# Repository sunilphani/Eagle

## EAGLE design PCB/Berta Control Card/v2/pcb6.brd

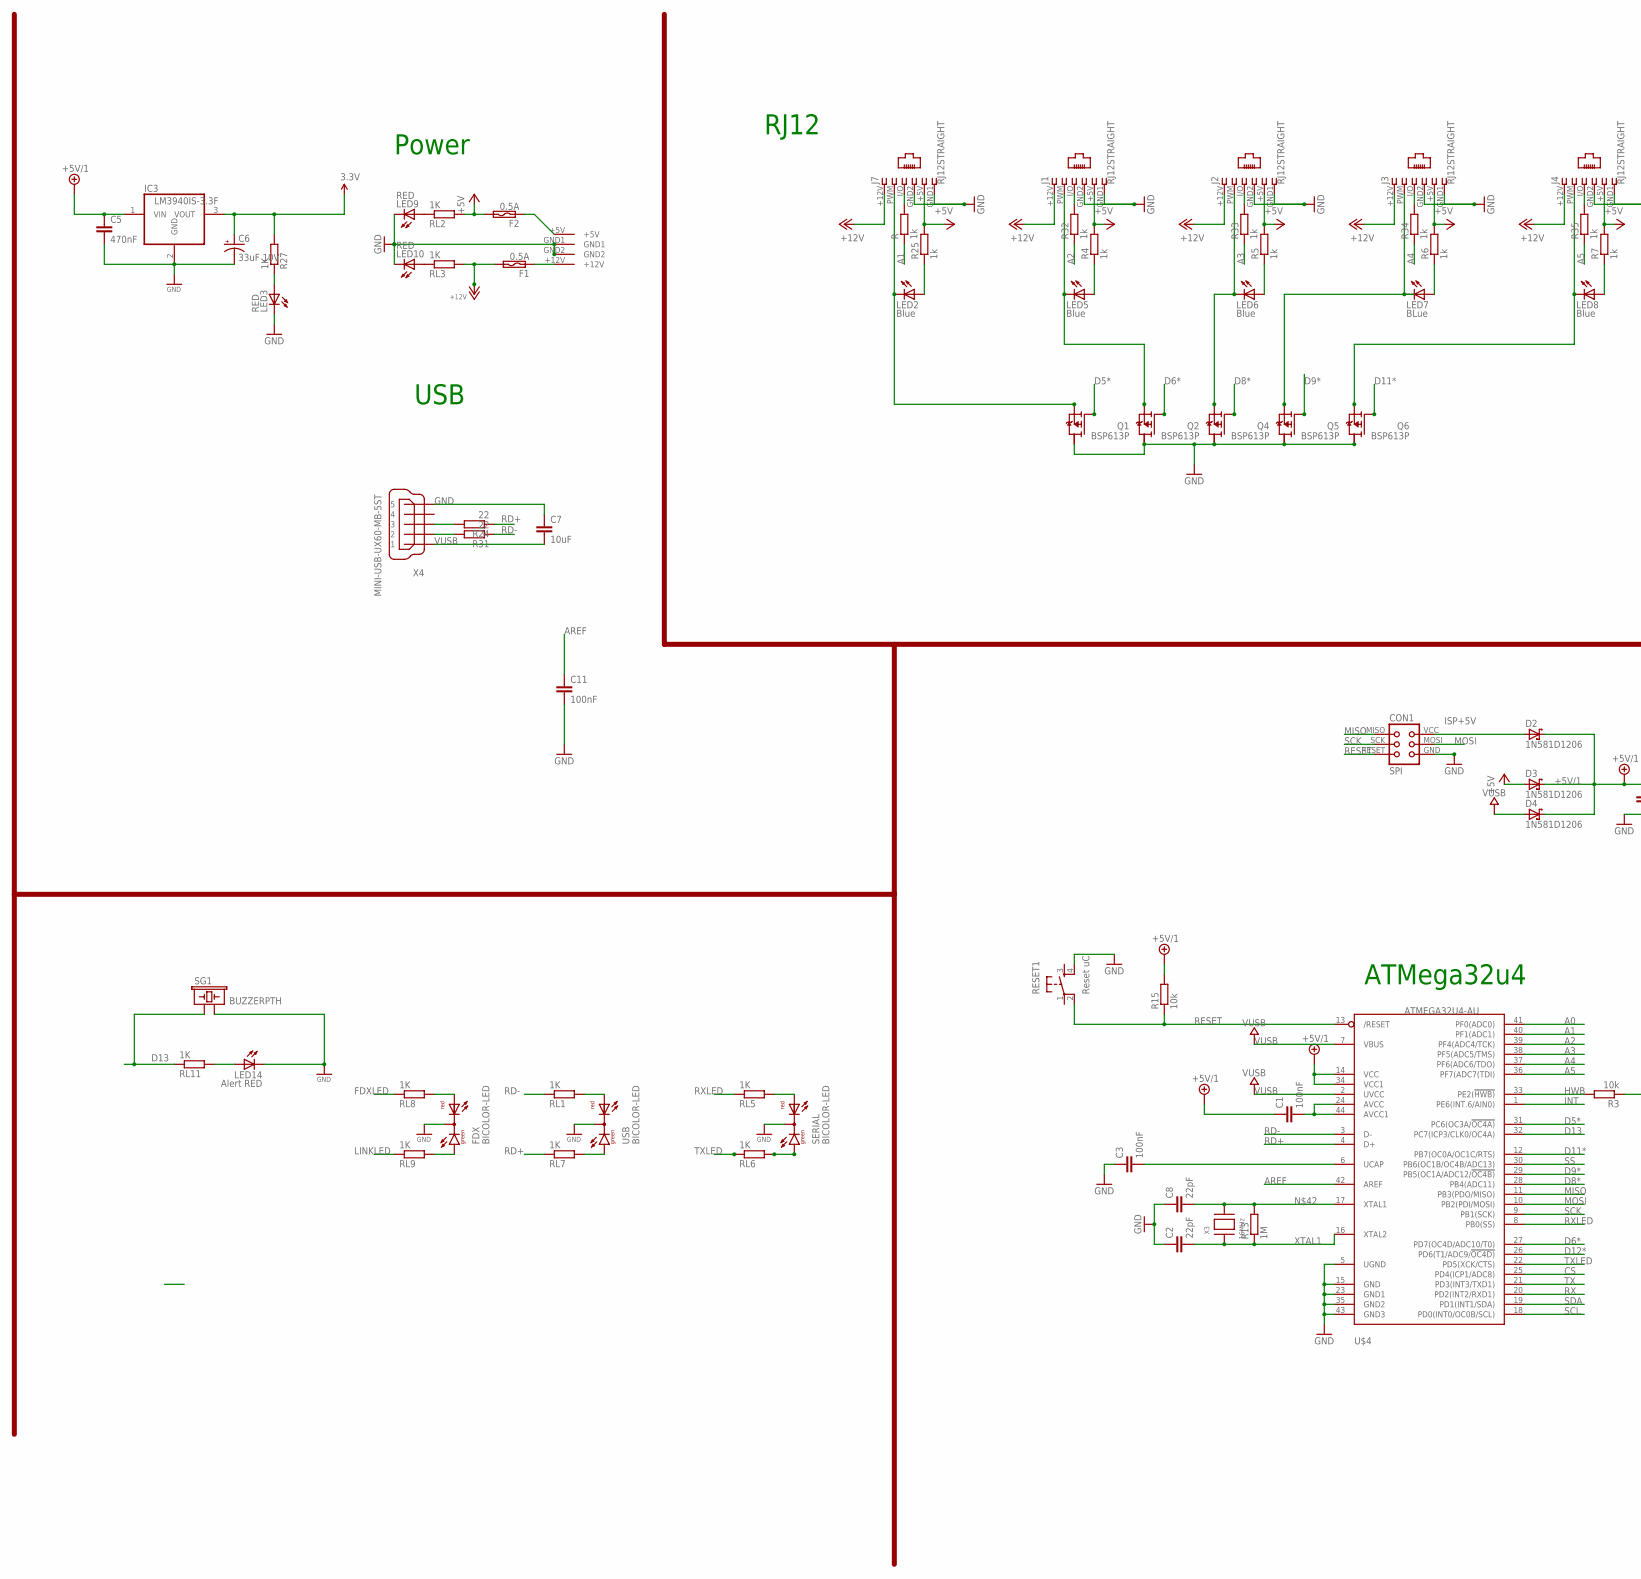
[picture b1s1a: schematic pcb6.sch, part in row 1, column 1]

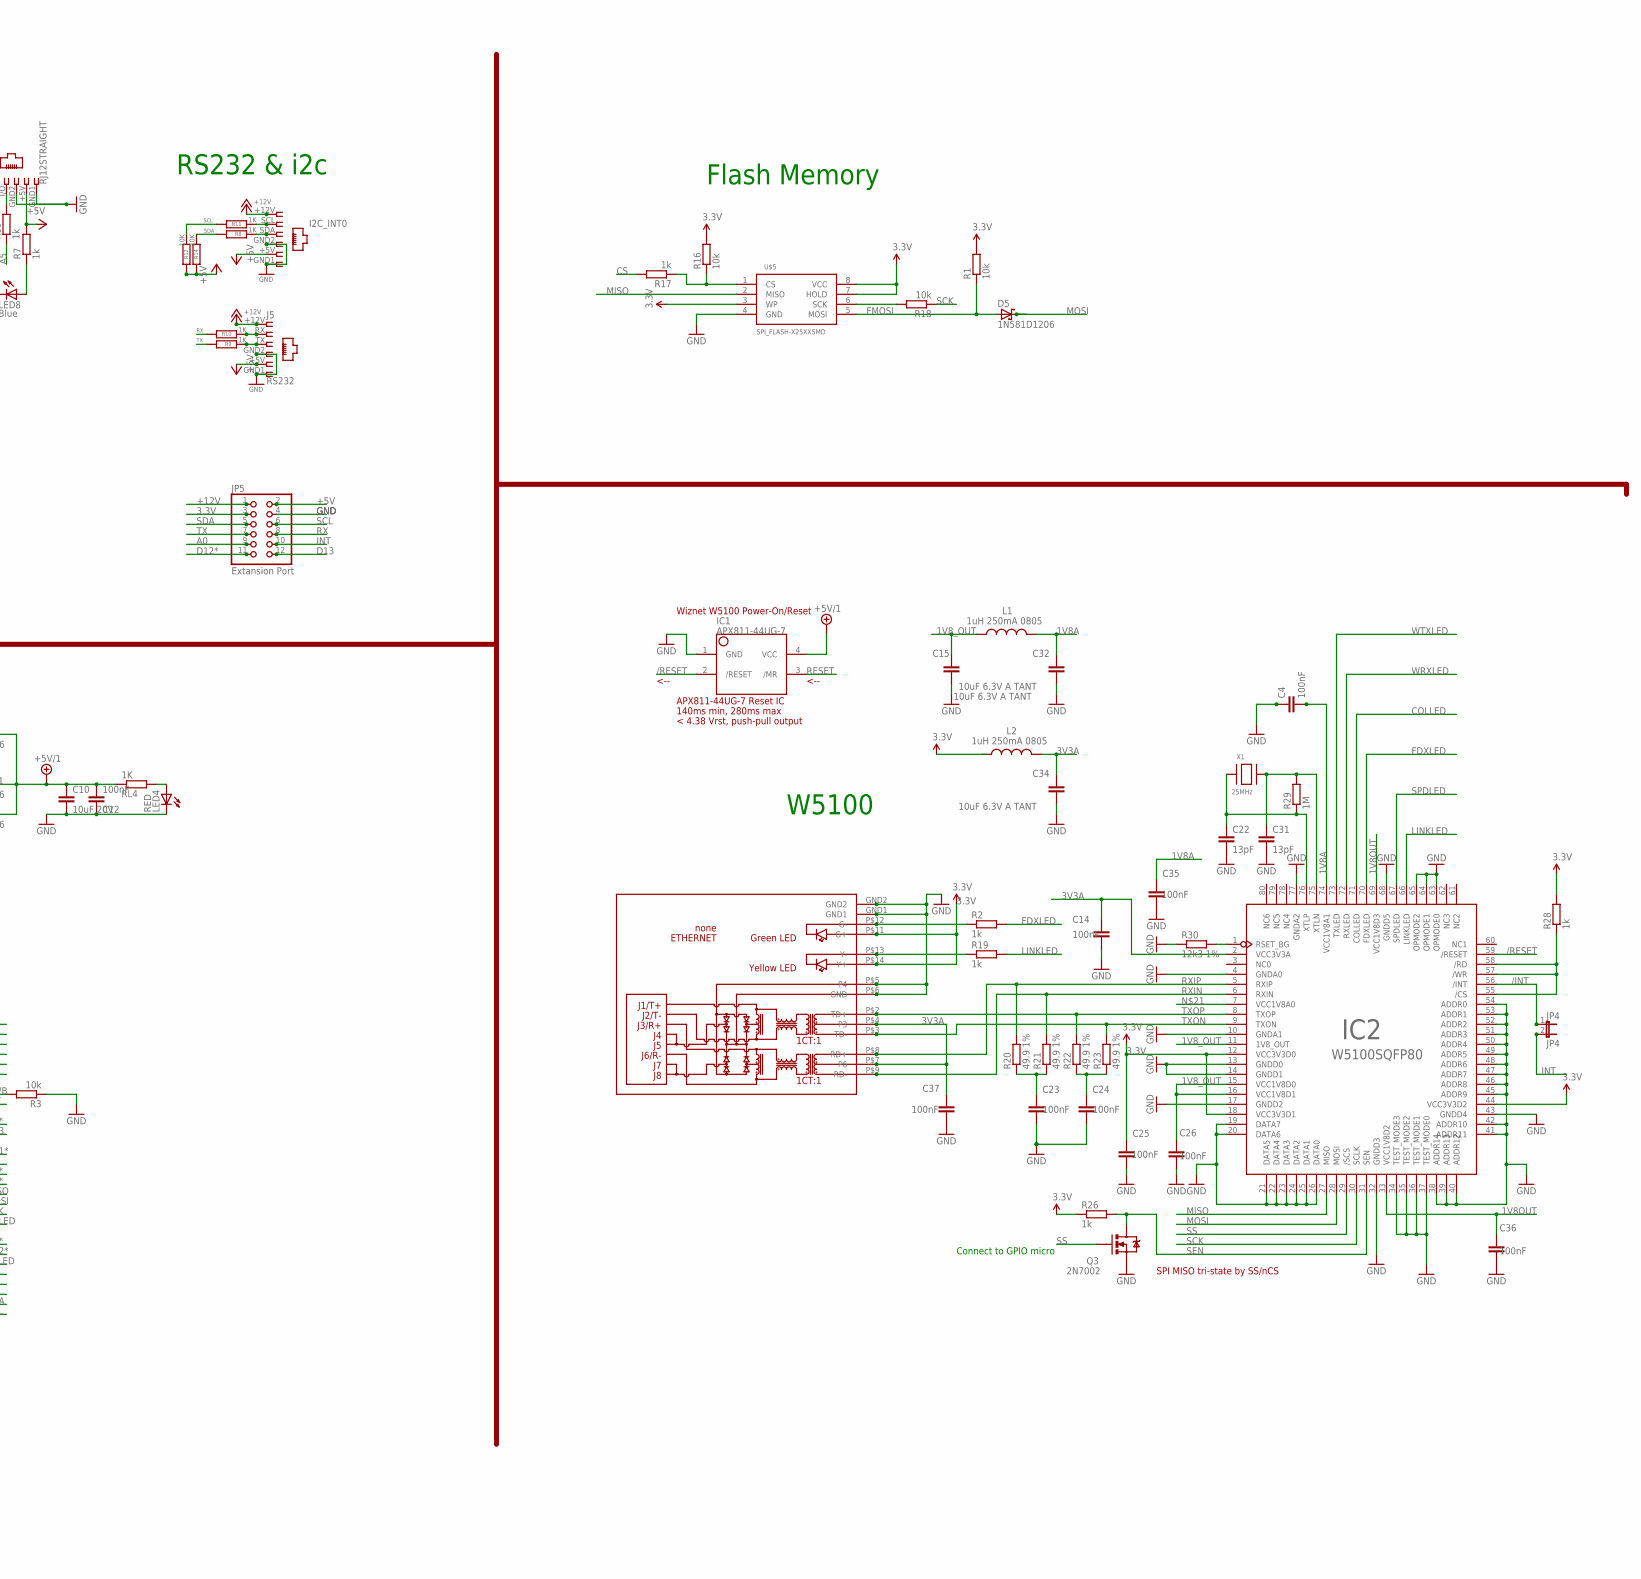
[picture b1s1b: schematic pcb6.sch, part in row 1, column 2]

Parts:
C1, C3, C4, C11, C12, C14, C23, C24, C25, C26, C35, C36, C37: 100nF; C1206
C2, C8: 22pF; C1206
C5: 470nF; C1206
C6: 33uF 10V; EIA7343
C7: 10uF; C1206
C10: 10uF 20V; C1206
C15, C32, C34: 10uF 6.3V A TANT; C1206
C22, C31: 13pF; C1206
CON1: SPI; TINYISP
D2, D3, D4, D5: 1N581D1206; LED-1206
ETHERNET: none; HY931147C
F1, F2: 0.5A; C1812
FDX: BICOLOR-LED; BICOLOR-3MM
I2C_INT0: I2C; RJ12-STRAIGHT-I2C
IC1: APX811-44UG-7; SOT143-R
IC2: W5100SQFP80; SQFP80
IC3: LM3940IS-3.3F; DD-3
J1, J2, J3, J4, J7: RJ12STRAIGHT; RJ12-STRAIGHT
J5: RS232; RJ12-STRAIGHT-RS232
JP4: JP4; 1X02
JP5: Extansion Port; 2X06
L1, L2: 1uH 250mA 0805; L2012C
LED2, LED5, LED6, LED8: Blue; LED3MM
LED3, LED4, LED9, LED10: RED; LED3MM
LED7: BLue; LED3MM
LED14: Alert RED; LED3MM
Q1, Q2, Q4, Q5, Q6: BSP613P; PG-SOT-223
Q3: 2N7002; SOT23-3
R, R2, R4, R5, R6, R7, R17, R19, R25, R26, R28, R32, R33, R34, R35: 1k; R0805
R1, R3, R15, R16, R18: 10k; R1206
R8, R9, R10, R11, R27: 1K; R0805
R12, R14: 10K; R1206
R13, R29: 1M; R1206
R20, R21, R22, R23: 49.9 1%; R0805W
R24, R31: 22; M1206
R30: 12k3 1%; R0805W
RESET1: Reset uC; TACTILE_SWITCH_SMD
RL1, RL2, RL3, RL5, RL6, RL7, RL8, RL9, RL11: 1K; R0805
RL4: 1K; R0805@1
SERIAL: BICOLOR-LED; BICOLOR-3MM
SG1: BUZZERPTH; BUZZER-12MM
U$4: ATMEGA32U4-AU; TQFP44
U$5: SPI_FLASH-X25XXSMD; SO08
U$6: KPJX-4S-S
USB: BICOLOR-LED; BICOLOR-3MM
X1: 25MHz; NX6035
X3: 16MHz; NX6035
X4: MINI-USB-UX60-MB-5ST; UX60-MB-5ST

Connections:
1V8A: C4.2, C32.1, C35.1, IC2.74 (VCC1V8A1), L1.2
1V8OUT: C36.1, IC2.33 (VCC1V8D2), IC2.69 (VCC1V8D3)
1V8_OUT: C15.1, C26.1, IC2.11 (1V8_OUT), IC2.15 (VCC1V8D0), IC2.16 (VCC1V8D1), L1.1
3.3V: C6.A (+), C25.1, ETHERNET.P$11 (G+), ETHERNET.P$14 (Y+), IC2.12 (VCC3V3D0), IC2.18 (VCC3V3D1), IC2.44 (VCC3V3D2), IC3.3 (VOUT), JP5.3, R1.2, R16.2, R26.1, R27.2, R28.2, U$5.3 (WP), U$5.7 (HOLD), U$5.8 (VCC)
3V3A: C14.1, C34.1, C37.1, ETHERNET.P$4 (P3), ETHERNET.P$7 (P6), IC2.2 (VCC3V3A), L2.2
+5V: D3.A, F2.2, I2C_INT0.+5V (5), J1.+5V (5), J2.+5V (5), J3.+5V (5), J4.+5V (5), J5.+5V (5), J7.+5V (5), JP5.2, R4.2, R5.2, R6.2, R7.2, R12.2, R14.2, R25.2, RL2.2
+5V/1: C1.1, C5.1, C10.1, C12.2, D2.C, D3.C, D4.C, IC1.4 (VCC), IC3.1 (VIN), R15.2, RL4.1, U$4.14 (VCC), U$4.34 (VCC1)
+12V: F1.2, I2C_INT0.+12V (1), J1.+12V (1), J2.+12V (1), J3.+12V (1), J4.+12V (1), J5.+12V (1), J7.+12V (1), JP5.1, RL3.2
/INT: IC2.56 (/INT), JP4.1
/RESET: IC1.2 (/RESET), IC2.59 (/RESET)
A0: JP5.9, U$4.41 (PF0(ADC0))
A1: R.1, U$4.40 (PF1(ADC1))
A2: R32.1, U$4.39 (PF4(ADC4/TCK))
A3: R33.1, U$4.38 (PF5(ADC5/TMS))
A4: R34.1, U$4.37 (PF6(ADC6/TDO))
A5: R35.1, U$4.36 (PF7(ADC7(TDI))
AREF: C11.1, U$4.42 (AREF)
COLLED: IC2.71 (COLLED)
CS: R17.2, U$4.25 (PD4(ICP1/ADC8))
D2B4: I2C_INT0.SDA (3), R8.1
D2B5: J5.TX (3), R9.1
D5*: Q1.1 (G), U$4.31 (PC6(OC3A/!OC4A))
D6*: Q2.1 (G), U$4.27 (PD7(OC4D/ADC10/T0))
D8*: Q4.1 (G), U$4.28 (PB4(ADC11))
D9*: Q5.1 (G), U$4.29 (PB5(OC1A/ADC12/!OC4B))
D11*: Q6.1 (G), U$4.12 (PB7(OC0A/OC1C/RTS))
D12*: JP5.11, U$4.26 (PD6(T1/ADC9/!OC4D))
D13: JP5.12, RL11.1, SG1.+ (1), U$4.32 (PC7(ICP3/CLK0/OC4A))
D+USB: R24.2, X4.3
D-USB: R31.2, X4.2
FDXLED: IC2.70 (FDXLED), R2.2, RL8.1
FMOSI: D5.A, R1.1, U$5.5 (MOSI)
GND: C2.1, C3.1, C4.1, C5.2, C6.C (-), C7.1, C8.1, C10.2, C11.2, C12.1, C14.2, C15.2, C22.2, C23.2, C24.2, C25.2, C26.2, C31.2, C32.2, C34.2, C35.2, C36.2, C37.2, CON1.GND, ETHERNET.GND1, ETHERNET.GND2, ETHERNET.P$5 (P4), ETHERNET.P$6 (GND), FDX.2 (C), I2C_INT0.GND1 (6), I2C_INT0.GND2 (4), IC1.1 (GND), IC2.4 (GNDA0), IC2.10 (GNDA1), IC2.13 (GNDD0), IC2.14 (GNDD1), IC2.17 (GNDD2), IC2.19 (DATA7), IC2.20 (DATA6), IC2.21 (DATA5), IC2.22 (DATA4), IC2.23 (DATA3), IC2.24 (DATA2), IC2.25 (DATA1), IC2.26 (DATA0), IC2.32 (GNDD3), IC2.34 (TEST_MODE3), IC2.35 (TEST_MODE2), IC2.36 (TEST_MODE1), IC2.37 (TEST_MODE0), IC2.38 (ADDR14), IC2.39 (ADDR13), IC2.40 (ADDR12), IC2.41 (ADDR11), IC2.42 (ADDR10), IC2.43 (GNDD4), IC2.45 (ADDR9), IC2.46 (ADDR8), IC2.47 (ADDR7), IC2.48 (ADDR6), IC2.49 (ADDR5), IC2.50 (ADDR4), IC2.51 (ADDR3), IC2.52 (ADDR2), IC2.53 (ADDR1), IC2.54 (ADDR0), IC2.63 (OPMODE0), IC2.64 (OPMODE1), IC2.65 (OPMODE2), IC2.68 (GNDD5), IC2.77 (GNDA2), IC3.2 (GND), J1.GND1 (6), J1.GND2 (4), J2.GND1 (6), J2.GND2 (4), J3.GND1 (6), J3.GND2 (4), J4.GND1 (6), J4.GND2 (4), J5.GND1 (6), J5.GND2 (4), J7.GND1 (6), J7.GND2 (4), JP5.4, LED3.K (C), LED4.K (C), LED9.K (C), LED10.K (C), LED14.K (C), Q1.2 (D), Q2.2 (D), Q3.2 (S), Q4.2 (D), Q5.2 (D), Q6.2 (D), R3.1, R30.1, RESET1.4, SERIAL.2 (C), SG1.- (2), U$4.5 (UGND), U$4.15 (GND), U$4.23 (GND1), U$4.35 (GND2), U$4.43 (GND3), U$5.4 (GND), U$6.GND1, U$6.GND2, USB.2 (C), X4.5
HWB: R3.2, U$4.33 (PE2(!HWB))
INT: JP4.2, JP5.10, U$4.1 (PE6(INT.6/AIN0))
ISP+5V: CON1.VCC, D2.A
LINKLED: IC2.66 (LINKLED), R19.2, RL9.1
MISO: CON1.MISO, IC2.27 (MISO), U$4.11 (PB3(PDO/MISO)), U$5.2 (MISO)
MOSI: CON1.MOSI, D5.C, IC2.28 (MOSI), U$4.10 (PB2(PDI/MOSI))
unnamed: J2.PWM (2), LED6.K (C), Q4.3 (S)
unnamed: J1.I/O (3), R32.2
unnamed: C1.2, U$4.24 (AVCC), U$4.44 (AVCC1)
unnamed: LED5.A, R4.1
unnamed: J3.PWM (2), LED7.K (C), Q5.3 (S)
unnamed: FDX.3 (AR), RL8.2
unnamed: J2.I/O (3), R33.2
unnamed: RL1.2, USB.3 (AR)
unnamed: C24.1, R22.1, R23.1
unnamed: R16.1, R17.1, U$5.1 (CS)
unnamed: FDX.1 (AG), RL9.2
unnamed: LED4.A, RL4.2
unnamed: RL5.2, SERIAL.3 (AR)
unnamed: RL7.2, USB.1 (AG)
unnamed: RL6.2, SERIAL.1 (AG)
unnamed: C3.2, U$4.6 (UCAP)
unnamed: LED2.A, R25.1
unnamed: J7.I/O (3), R.2
unnamed: J4.PWM (2), LED8.K (C), Q6.3 (S)
unnamed: LED3.A, R27.1
unnamed: LED6.A, R5.1
unnamed: R18.2, U$5.6 (SCK)
unnamed: IC2.55 (/CS), IC2.57 (/WR), IC2.58 (/RD), R28.1
unnamed: LED14.A, RL11.2
unnamed: J1.PWM (2), LED5.K (C), Q2.3 (S)
unnamed: J3.I/O (3), R34.2
unnamed: LED7.A, R6.1
unnamed: J4.I/O (3), R35.2
unnamed: LED8.A, R7.1
unnamed: J7.PWM (2), LED2.K (C), Q1.3 (S)
unnamed: F2.1, U$6.+5V
unnamed: F1.1, U$6.+12V
unnamed: C8.2, R13.2, U$4.17 (XTAL1), X3.P$2
unnamed: ETHERNET.P$12 (G-), R2.1
unnamed: J5.RX (2), R10.1
unnamed: I2C_INT0.SCL (2), R11.1
unnamed: LED10.A, RL3.1
unnamed: LED9.A, RL2.1
unnamed: C23.1, R20.1, R21.1
unnamed: IC2.1 (RSET_BG), R30.2
unnamed: ETHERNET.P$13 (Y-), R19.1
RD+: R24.1, RL7.1, U$4.4 (D+)
RD-: R31.1, RL1.1, U$4.3 (D-)
RESET: CON1.RESET, IC1.3 (/MR), R15.1, RESET1.2, U$4.13 (/RESET)
RX: JP5.8, R10.2, U$4.20 (PD2(INT2/RXD1))
RXIN: ETHERNET.P$9 (RD-), IC2.6 (RXIN), R21.2
RXIP: ETHERNET.P$8 (RD+), IC2.5 (RXIP), R20.2
RXLED: RL5.1, U$4.8 (PB0(SS))
SCK: CON1.SCK, IC2.30 (SCLK), R18.1, U$4.9 (PB1(SCK))
SCL: JP5.6, R11.2, R12.1, U$4.18 (PD0(INT0/OC0B/SCL))
SDA: JP5.5, R8.2, R14.1, U$4.19 (PD1(INT1/SDA))
SEN: IC2.31 (SEN), Q3.3 (D), R26.2
SPDLED: IC2.67 (SPDLED)
SS: IC2.29 (/SCS), Q3.1 (G), U$4.30 (PB6(OC1B/OC4B/ADC13))
TX: JP5.7, R9.2, U$4.21 (PD3(INT3/TXD1))
TXLED: RL6.1, U$4.22 (PD5(XCK/CTS))
TXON: ETHERNET.P$3 (TD-), IC2.9 (TXON), R23.2
TXOP: ETHERNET.P$2 (TD+), IC2.8 (TXOP), R22.2
VUSB: C7.2, D4.A, U$4.2 (UVCC), U$4.7 (VBUS), X4.1
WRXLED: IC2.72 (RXLED)
WTXLED: IC2.73 (TXLED)
XTAL1: C2.2, R13.1, U$4.16 (XTAL2), X3.P$1
XTLN: C31.1, IC2.75 (XTLN), R29.2, X1.P$2
XTLP: C22.1, IC2.76 (XTLP), R29.1, X1.P$1

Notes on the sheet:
Flash Memory
RJ12
ATMega32u4
W5100
USB
Power
RS232 & i2c
SPI MISO tri-state by SS/nCS
Connect to GPIO micro
APX811-44UG-7 Reset IC
140ms min, 280ms max
Wiznet W5100 Power-On/Reset
< 4.38 Vrst, push-pull output
<--

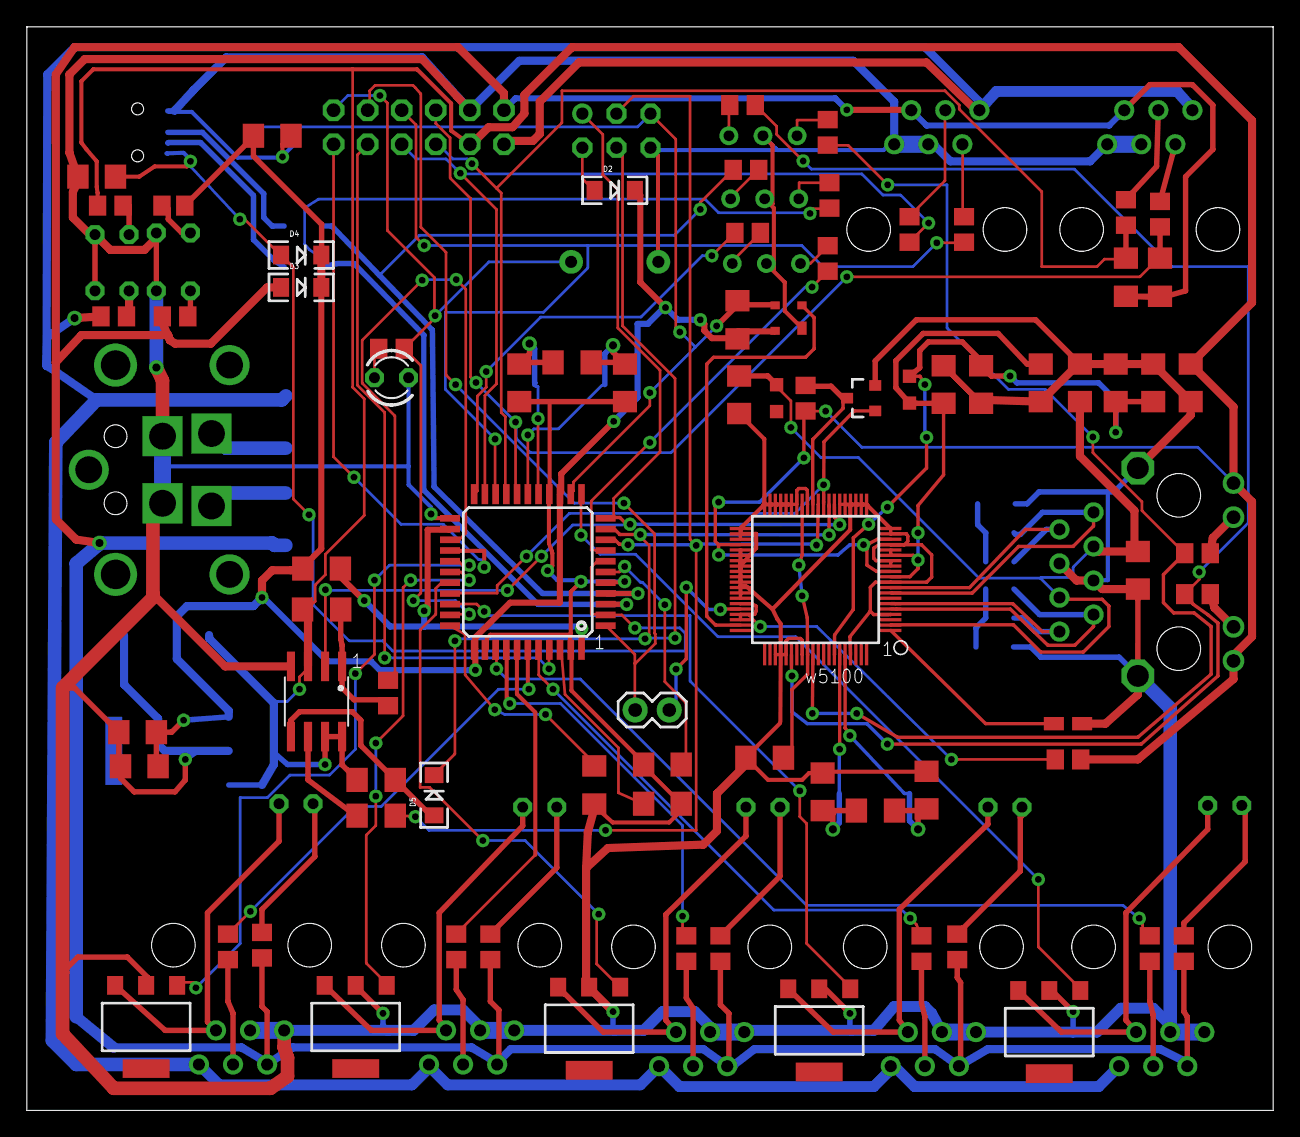
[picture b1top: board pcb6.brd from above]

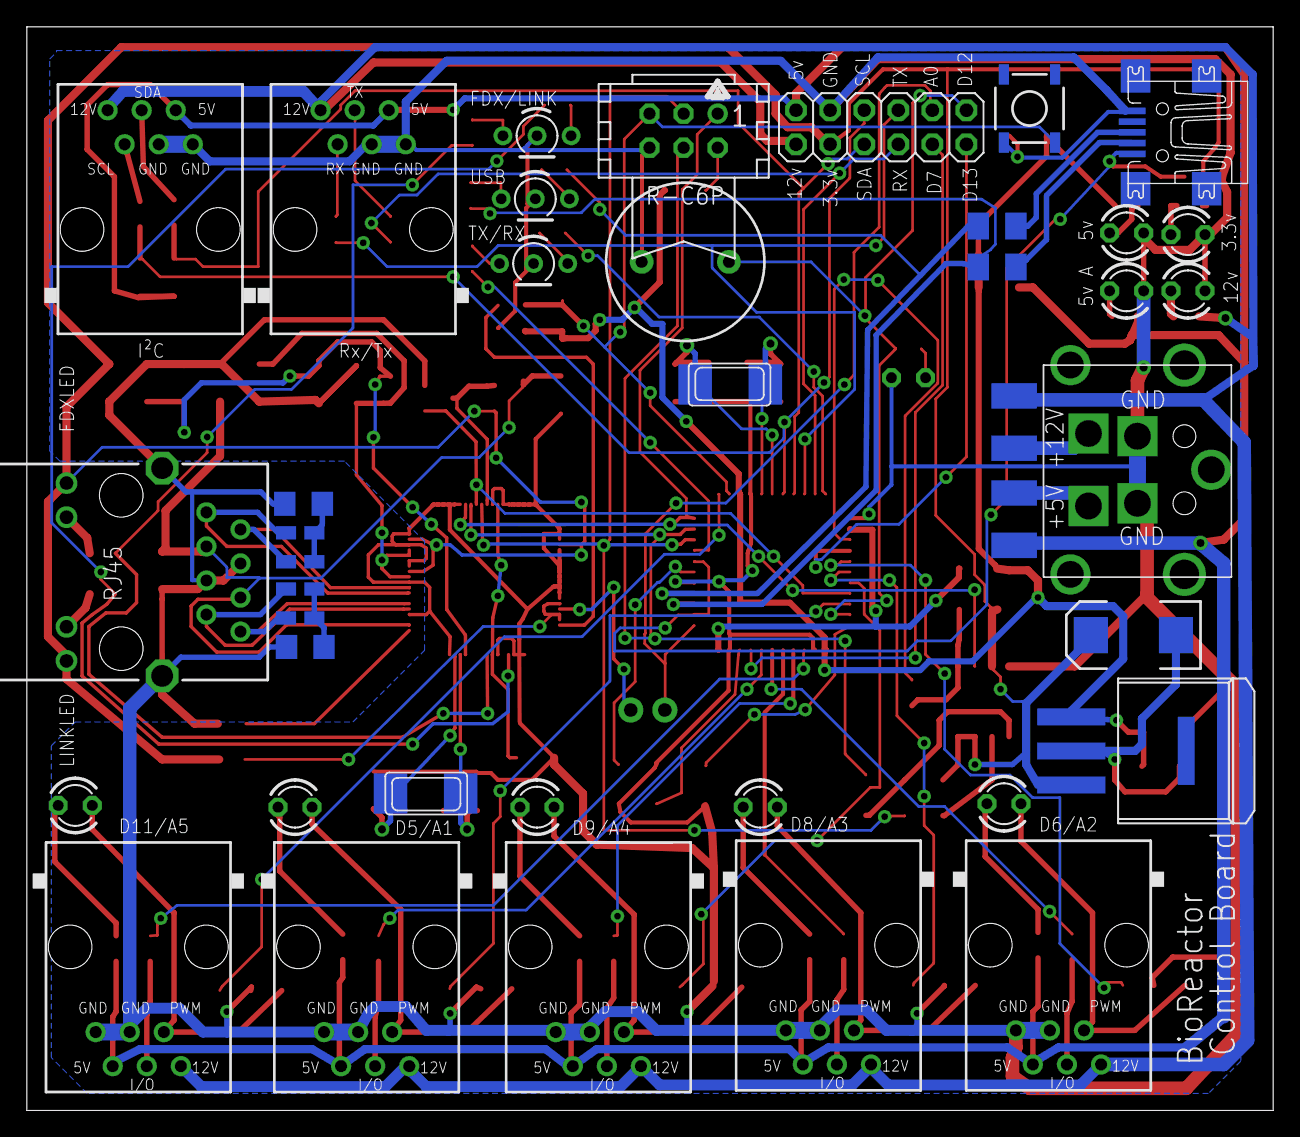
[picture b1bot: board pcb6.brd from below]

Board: 2 copper layers, 92.9 x 80.8 mm, 119 parts (40 on the bottom side), 99 nets.

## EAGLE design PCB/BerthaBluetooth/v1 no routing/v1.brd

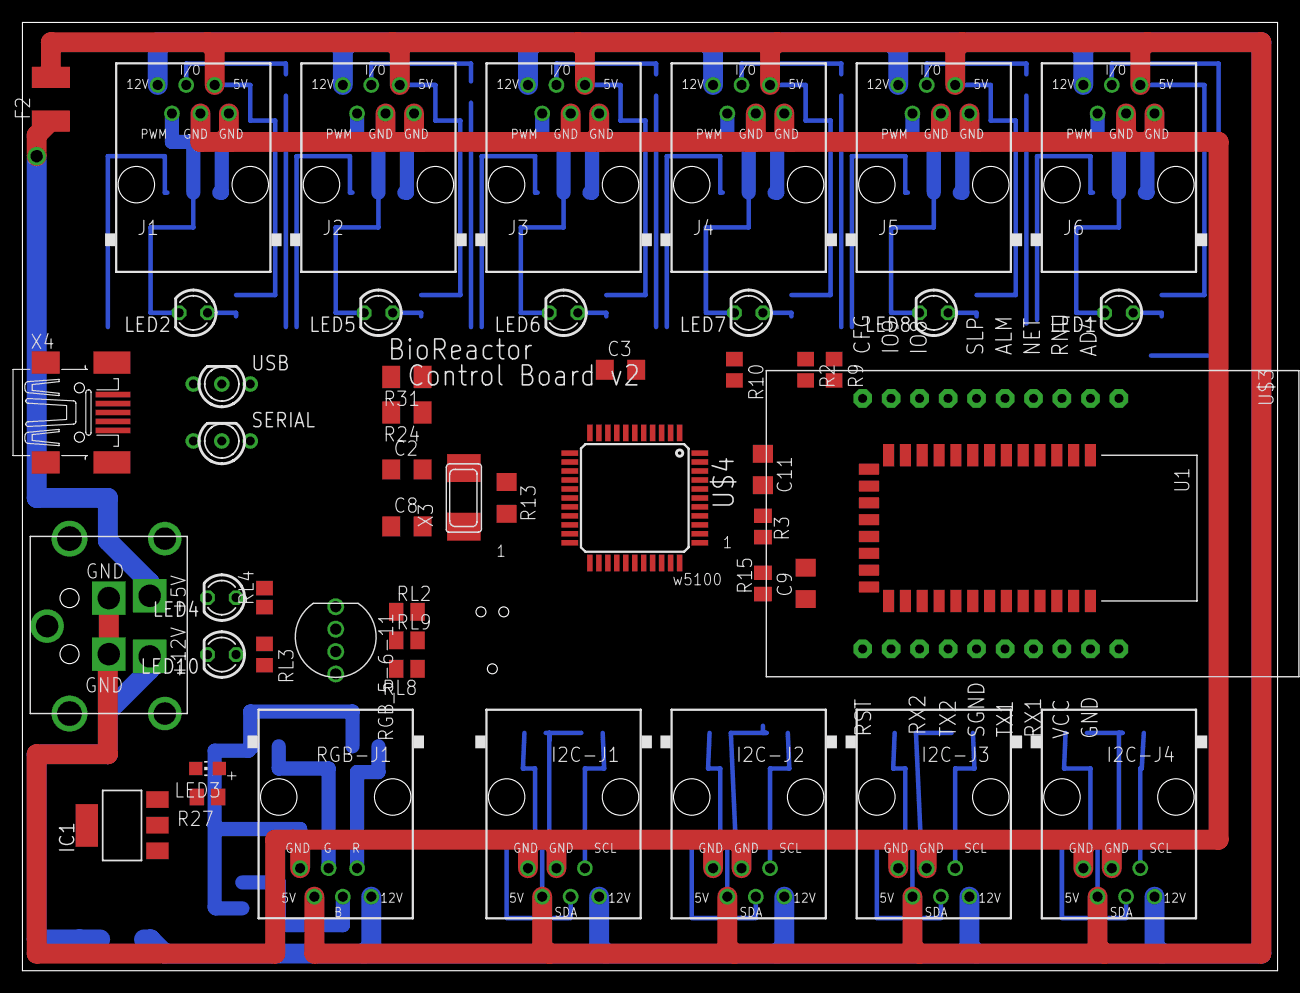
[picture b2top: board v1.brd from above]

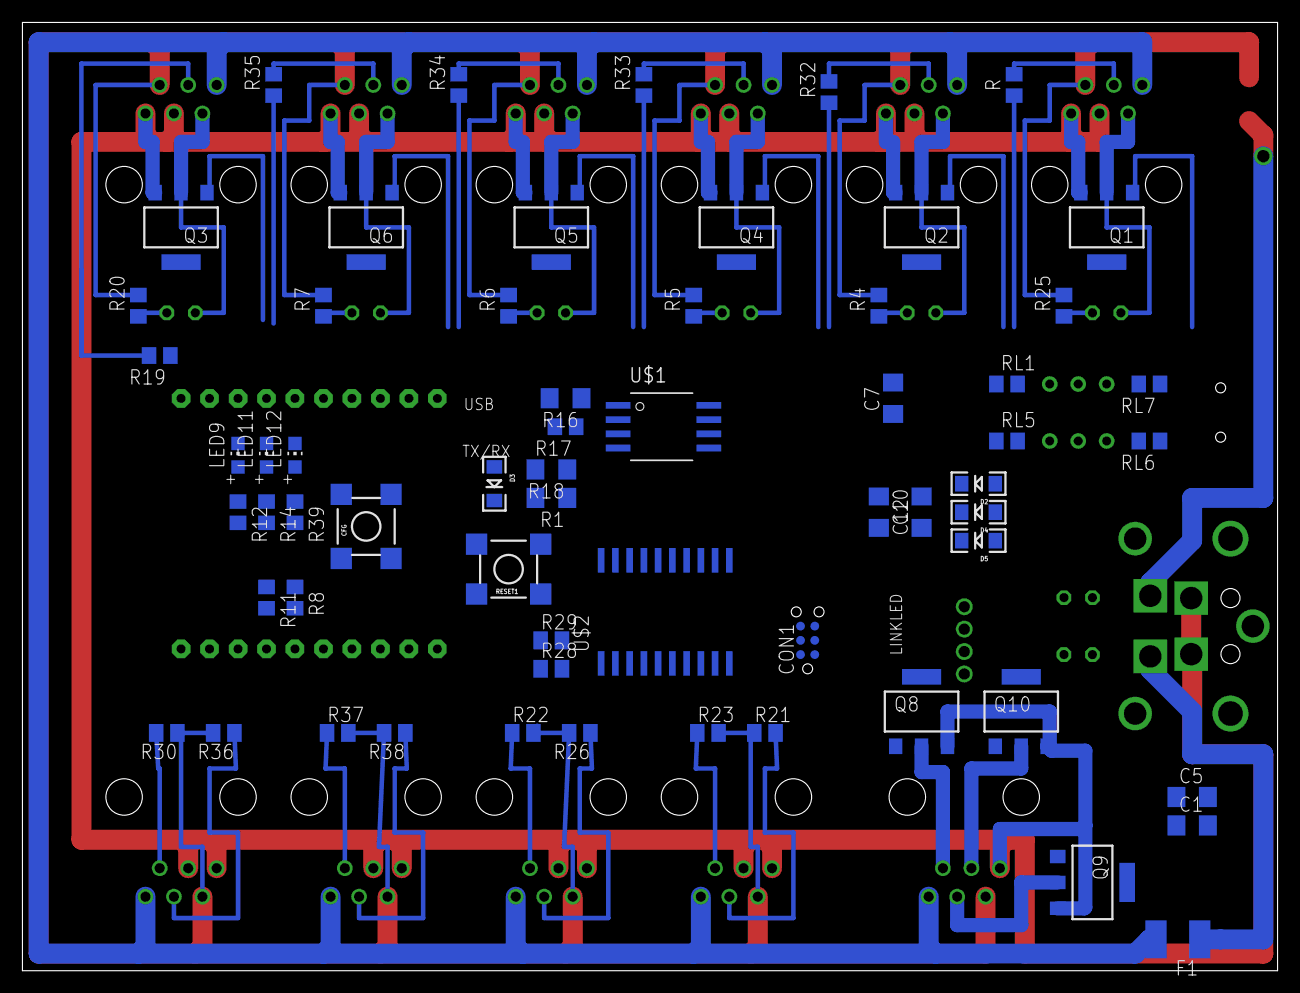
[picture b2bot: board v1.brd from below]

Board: 2 copper layers, 111.9 x 84.6 mm, 112 parts (62 on the bottom side), 97 nets.

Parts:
C1, C5, C7, C10: 10uF; C1206
C2, C8: 22pF; C1206
C3, C9, C11, C12: 100nF; C1206
CFG: Configure; TACTILE_SWITCH_SMD
CON1: SPI; TC2030-MCP-NL
D2, D3, D4, D5: 1N581D1206; LED-1206
F1, F2: 0.5A; C1812
I2C-J1, I2C-J2, I2C-J3, I2C-J4: RJ12STRAIGHT-I2C; RJ12-STRAIGHT-I2C
IC1: REG1117; SOT223
J1, J2, J3, J4, J5, J6: RJ12; RJ12-STRAIGHT
LED1, LED2, LED5, LED6, LED8: Blue; LED3MM
LED3, LED9, LED11, LED12: RED; CHIP-LED0805
LED4, LED10: RED; LED3MM
LED7: BLue; LED3MM
Q1, Q2, Q3, Q4, Q5, Q6, Q8, Q9, Q10: BSP613P; PG-SOT-223
R, R4, R6, R7, R17, R19, R20, R32, R34, R35: 1k; R0805
R1, R16, R18: 10k; R1206
R2: 2.2K; R0805
R3, R15: 10k; M0805
R5, R25, R33: RJ12; R0805
R8, R10, R11, R12, R14, R27, R39: 1K; R0805
R9: 1.2K; R0805
R13: 1M; R1206
R21, R22, R23, R26, R28, R29, R30, R36, R37, R38: 10K; M0805
R24, R31: 22; M1206
RESET1: Reset uC; TACTILE_SWITCH_SMD
RGB-J1: RJ12; RJ12-STRAIGHT-RGB
RGB_5-6-11: LED-TRICOLOR-THROUGHHOLE
RL1, RL3, RL4, RL5, RL6, RL7: 1K; R0805
RL2, RL8, RL9: 1K; M0805
SERIAL: BICOLOR-LED; BICOLOR-3MM
U1: HC_05; BLUETOOTH_SMD
U$1: SST25VF064C; SOIC_8-LEAD
U$2: PCA9518; SO20W
U$3: SZ05-ZIGBEE
U$4: ATMEGA32U4-AU; TQFP44
U$6: KPJX-4S-S
USB: BICOLOR-LED; BICOLOR-3MM
X3: 16MHz; NX6035
X4: MINI-USB-SCHIELD-32005-201; 32005-201

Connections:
3.3V: C1.1, IC1.2, R1.2, R16.2, R27.2, U1.12, U$1.RST/HOLD, U$1.VDD, U$1.WP, U$2.20
+5V: D3.A, F2.2, I2C-J1.+5V, I2C-J2.+5V, I2C-J3.+5V, I2C-J4.+5V, J1.+5V, J2.+5V, J3.+5V, J4.+5V, J5.+5V, J6.+5V, R4.2, R5.2, R6.2, R7.2, R12.2, R14.2, R20.2, R21.1, R22.2, R23.2, R25.2, R26.2, R28.1, R29.1, R30.1, R36.2, R37.2, R38.2, R39.2, RGB-J1.+5V, U$3.VCC
+5V/1: C5.1, C10.1, C12.2, D2.C, D3.C, D4.C, IC1.3, R15.2, RL4.1, U$4.2, U$4.14, U$4.24, U$4.34, U$4.44
+12V: F1.2, I2C-J1.+12V, I2C-J2.+12V, I2C-J3.+12V, I2C-J4.+12V, J1.+12V, J2.+12V, J3.+12V, J4.+12V, J5.+12V, J6.+12V, RGB-J1.+12V, RL3.2
A0: R35.1, U$4.36
A1: R33.1, U$4.37
A2: R32.1, U$4.38
A3: R.1, U$4.39
A4: R34.1, U$4.40
A5: R19.1, U$4.41
AREF: C11.1, U$4.42
CS: R17.2, U$4.25
D2B5: R2.1, R9.1, U1.2
D5*: Q5.1, U$4.31
D6*: Q1.1, U$4.27
D7*: Q10.1, U$4.1
D8*: Q2.1, U$4.28
D9*: Q4.1, U$4.29
D10*: Q3.1, U$4.30
D11*: Q6.1, U$4.12
D12*: Q8.1, U$4.26
D13*: Q9.1, U$4.32
D+USB: R24.2, X4.3
D-USB: R31.2, X4.2
FMOSI: D5.A, R1.1, U$1.SI
GND: C1.2, C2.1, C3.1, C5.2, C7.1, C8.1, C9.2, C10.2, C11.2, C12.1, CFG.1, CON1.GND, I2C-J1.GND1, I2C-J1.GND2, I2C-J2.GND1, I2C-J2.GND2, I2C-J3.GND1, I2C-J3.GND2, I2C-J4.GND1, I2C-J4.GND2, IC1.1, J1.GND1, J1.GND2, J2.GND1, J2.GND2, J3.GND1, J3.GND2, J4.GND1, J4.GND2, J5.GND1, J5.GND2, J6.GND1, J6.GND2, LED3.C, LED4.K, LED10.K, Q1.3, Q2.3, Q3.3, Q4.3, Q5.3, Q6.3, Q8.3, Q9.3, Q10.3, R2.2, R3.1, RESET1.4, RGB-J1.GND1, RGB_5-6-11.GND, SERIAL.2, U1.13, U$1.VSS, U$2.10, U$3.GND, U$3.SGND, U$4.5, U$4.15, U$4.23, U$4.35, U$4.43, U$6.GND1, U$6.GND2, USB.2, X4.5
GND1: LED9.C, U$3.RNU
GND2: LED11.C, U$3.NET
GND3: LED12.C, U$3.ALM
HWB: R3.2, U$4.33
ISP+5V: CON1.5V, D2.A
MISO: CON1.MISO, U$1.SO, U$4.11
MOSI: CON1.MOSI, D5.C, U$4.10
unnamed: J3.PWM, LED6.K, Q4.2
unnamed: J2.I/O, R32.2
unnamed: J6.I/O, R19.2
unnamed: LED5.A, R4.1
unnamed: J4.PWM, LED7.K, Q5.2
unnamed: Q10.2, RGB-J1.G, RL9.1
unnamed: J3.I/O, R33.2
unnamed: RL1.2, USB.3
unnamed: LED1.A, R20.1
unnamed: R16.1, R17.1, U$1.CE
unnamed: R11.2, U$3.RX1
unnamed: LED4.A, RL4.2
unnamed: RL5.2, SERIAL.3
unnamed: RL7.2, USB.1
unnamed: RL6.2, SERIAL.1
unnamed: C3.2, U$4.6
unnamed: LED2.A, R25.1
unnamed: J1.I/O, R.2
unnamed: J5.PWM, LED8.K, Q6.2
unnamed: LED3.A, R27.1
unnamed: J6.PWM, LED1.K, Q3.2
unnamed: LED6.A, R5.1
unnamed: R18.2, U$1.SCK
unnamed: R8.2, U$3.TX1
unnamed: LED9.A, R12.1
unnamed: LED11.A, R14.1
unnamed: LED12.A, R39.1
unnamed: J2.PWM, LED5.K, Q2.2
unnamed: J4.I/O, R34.2
unnamed: LED7.A, R6.1
unnamed: J5.I/O, R35.2
unnamed: LED8.A, R7.1
unnamed: J1.PWM, LED2.K, Q1.2
unnamed: CFG.4, U$3.CFG
unnamed: RGB_5-6-11.RED, RL2.2
unnamed: RGB_5-6-11.BLU, RL8.2
unnamed: F2.1, U$6.+5V
unnamed: F1.1, U$6.+12V
unnamed: RGB_5-6-11.GRN, RL9.2
unnamed: C8.2, R13.2, U$4.17, X3.P$2
unnamed: Q9.2, RGB-J1.B, RL8.1
unnamed: Q8.2, RGB-J1.R, RL2.1
unnamed: R10.1, U1.1
unnamed: LED10.A, RL3.1
RD+: R24.1, RL7.1, U$4.4
RD-: R31.1, RL1.1, U$4.3
RESET: C9.1, CON1.RESET, R15.1, RESET1.2, U$4.13
RX: R8.1, R10.2, U$4.20
RXLED: RL5.1, U$4.8
SCK: CON1.SCK, R18.1, U$4.9
SCL: R28.2, U$2.3, U$4.18
SCL1: I2C-J4.SCL, R30.2, U$2.5
SCL2: I2C-J3.SCL, R37.1, U$2.8
SCL3: I2C-J2.SCL, R22.1, U$2.12
SCL4: I2C-J1.SCL, R23.1, U$2.15
SDA: R29.2, U$2.4, U$4.19
SDA1: I2C-J4.SDA, R36.1, U$2.6
SDA2: I2C-J3.SDA, R38.1, U$2.9
SDA3: I2C-J2.SDA, R26.1, U$2.13
SDA4: I2C-J1.SDA, R21.2, U$2.16
TX: R9.2, R11.1, U$4.21
TXLED: RL6.1, U$4.22
VUSB: C7.2, D4.A, U$4.7, X4.1
XTAL1: C2.2, R13.1, U$4.16, X3.P$1

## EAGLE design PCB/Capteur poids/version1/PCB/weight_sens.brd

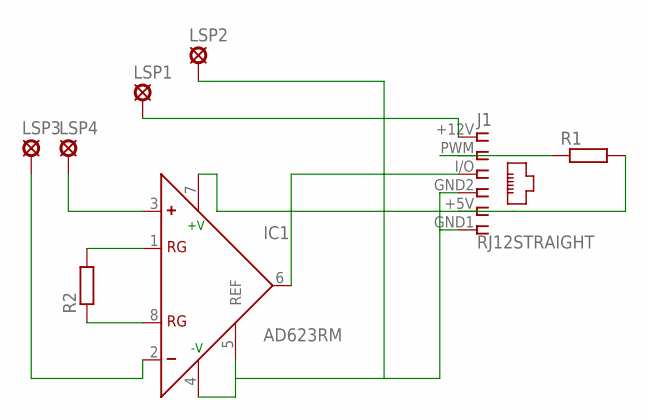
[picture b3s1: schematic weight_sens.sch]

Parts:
IC1: AD623RM; MSOP08
J1: RJ12STRAIGHT; RJ12-STRAIGHT
LSP1, LSP2, LSP3, LSP4: LSP10
R1: R-EU_M1206; M1206
R2: R-EU_R1206; R1206

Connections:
unnamed: IC1.1 (RG), R2.2
unnamed: IC1.8 (RG), R2.1
unnamed: IC1.6 (OUT), J1.I/O (3)
unnamed: IC1.2 (-), LSP3.MP
unnamed: IC1.7 (+V), J1.+5V (5), R1.2
unnamed: IC1.4 (-V), IC1.5 (REF), J1.GND1 (6), J1.GND2 (4), LSP2.MP
unnamed: J1.+12V (1), LSP1.MP
unnamed: IC1.3 (+), LSP4.MP
unnamed: J1.PWM (2), R1.1

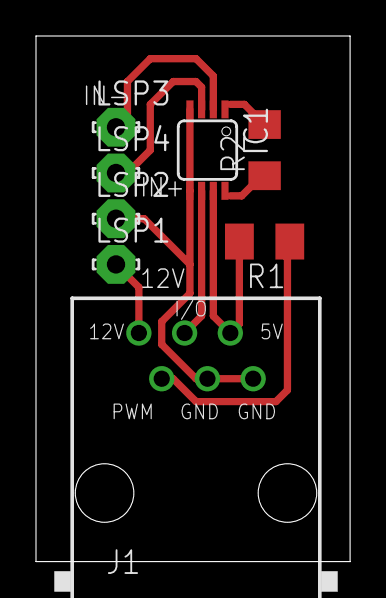
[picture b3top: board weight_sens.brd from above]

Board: 2 copper layers, 17.4 x 29.2 mm, 8 parts (0 on the bottom side), 9 nets.

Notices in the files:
parts and their libraries:
SparkFun: Licensing: CC v3.0 Share-Alike You are welcome to use this library for commercial purposes.
lpatiny: ©2009 ROFA.cz - modified and updated by Robert Darlington ‹rdarlington@gmail.com›
